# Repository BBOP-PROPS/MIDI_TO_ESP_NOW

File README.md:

# MIDI_TO_ESP_NOW
Intercept MIDI Keyboard Key Press and cause an action on a remote ESP Device.  

[ESP-NOW](https://www.espressif.com/en/products/software/esp-now/overview)

[ESP-NOW Example](https://randomnerdtutorials.com/esp-now-esp32-arduino-ide/)

[MIDI with Arduino](https://www.instructables.com/Send-and-Receive-MIDI-with-Arduino/)

When a student plays a key on the MIDI Keyboard, it should send a remote action throuh the ESP-NOW protocol.  Pressing the keyboard "C" key might turn on a light momentarily on a remote prop.  "D" might turn on a stepper motor on a different prop.

The "Master" will interface with the MIDI keyboard, and the majority of the programming will be on the Slaves.

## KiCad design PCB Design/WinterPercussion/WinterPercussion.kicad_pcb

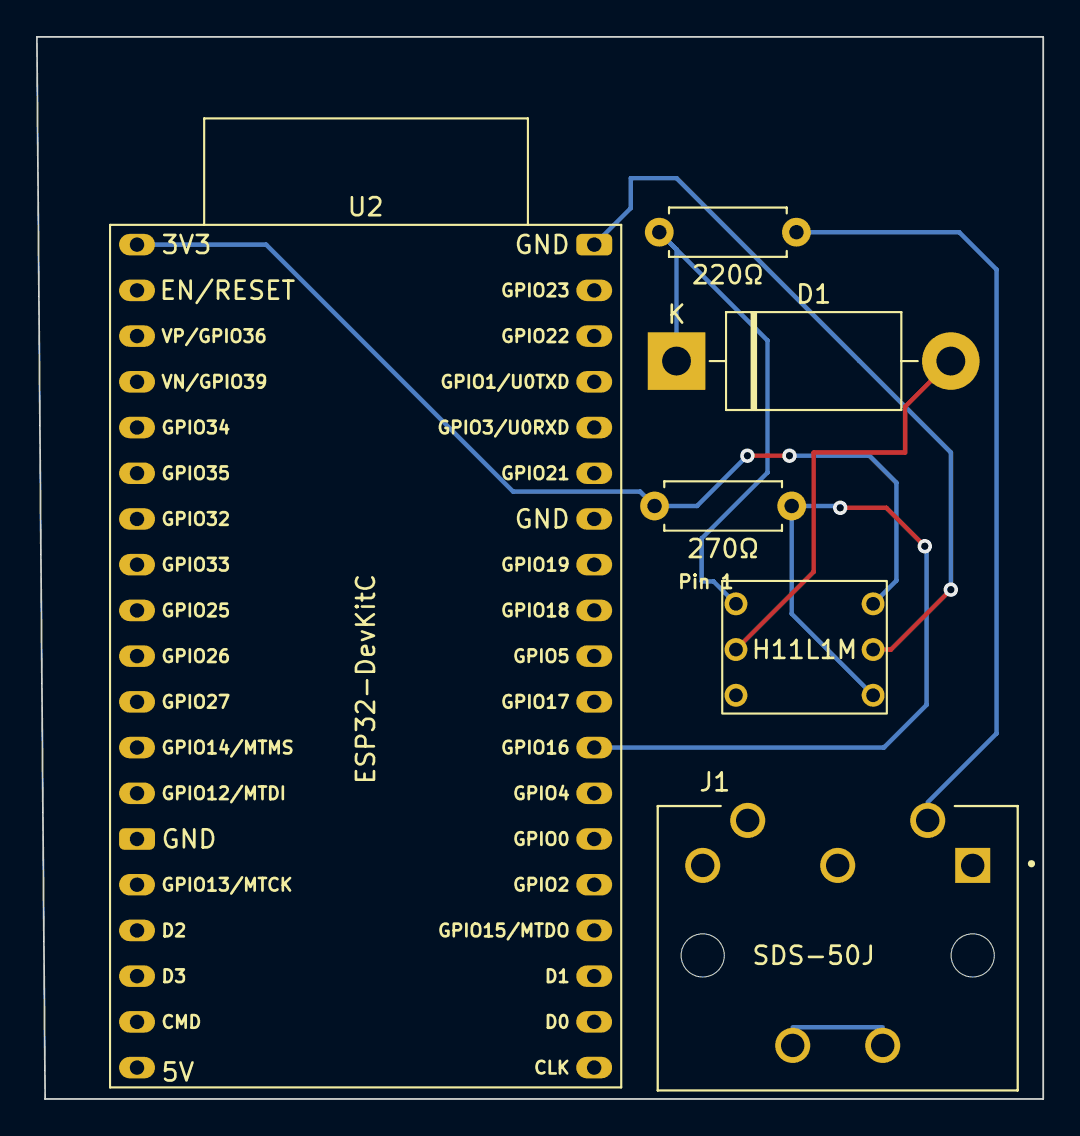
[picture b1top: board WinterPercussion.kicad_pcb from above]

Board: 2 copper layers, 55.9 x 59.0 mm, 6 parts (0 on the bottom side), 6 nets.

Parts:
D1: DIODE; D_DO-201AD_P15.24mm_Horizontal
J1: SDS-50J; CUI_SDS-50J
R1: 220Ω; R_Axial_DIN0207_L6.3mm_D2.5mm_P7.62mm_Horizontal
R2: 270Ω; R_Axial_DIN0207_L6.3mm_D2.5mm_P7.62mm_Horizontal
U1: H11L1M
U2: ESP32-DevKitC

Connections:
+3V3: R2.1, U1.6 (VCC), U2.1 (3V3)
ESP_PIN: R2.2, U1.4 (VO), U2.27 (GPIO16)
GND: U1.5 (GND), U2.38 (GND)
unnamed: J1.4, R1.2
unnamed: D1.2 (A), U1.2 (CATHODE)
unnamed: D1.1 (K), R1.1, U1.1 (ANODE)

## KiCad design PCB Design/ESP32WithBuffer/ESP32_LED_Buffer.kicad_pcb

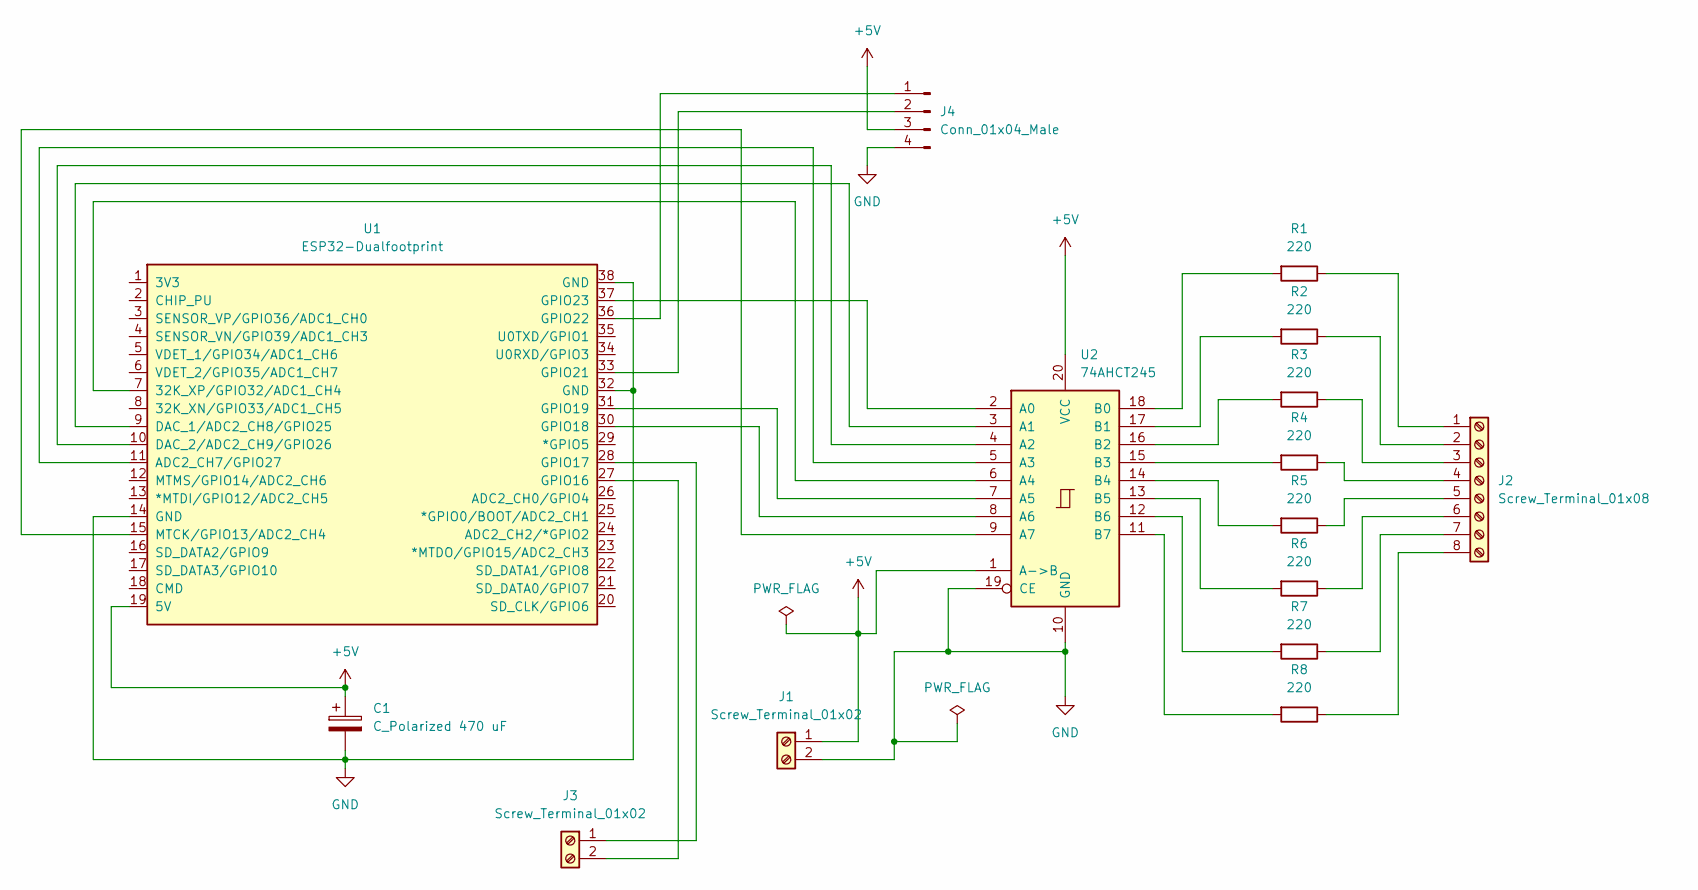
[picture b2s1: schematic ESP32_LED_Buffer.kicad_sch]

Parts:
C1: C_Polarized 470 uF; CP_Radial_D13.0mm_P7.50mm
J1, J3: Screw_Terminal_01x02; TerminalBlock_RND_205-00287_1x02_P5.08mm_Horizontal
J2: Screw_Terminal_01x08; TerminalBlock_RND_205-00293_1x08_P5.08mm_Horizontal
J4: Conn_01x04_Male; PinHeader_1x04_P2.54mm_Vertical
R1, R2, R3, R4, R5, R6, R7, R8: 220; R_Axial_DIN0207_L6.3mm_D2.5mm_P10.16mm_Horizontal
U1: ESP32-Dualfootprint; ESP32-DualFootprint
U2: 74AHCT245; DIP-20_W7.62mm

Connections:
+5V: C1.1, J1.1, J4.3, U1.19 (5V), U2.1 (A->B), U2.20 (VCC)
GND: C1.2, J1.2, J4.4, U1.14 (GND), U1.32 (GND), U1.38 (GND), U2.10 (GND), U2.19 (CE)
unnamed: J2.1, R1.1
unnamed: J2.2, R2.1
unnamed: J2.3, R3.1
unnamed: J2.4, R4.1
unnamed: J2.5, R5.1
unnamed: J2.6, R6.1
unnamed: J2.7, R7.1
unnamed: J2.8, R8.1
unnamed: R1.2, U2.18 (B0)
unnamed: R2.2, U2.17 (B1)
unnamed: R3.2, U2.16 (B2)
unnamed: R4.2, U2.15 (B3)
unnamed: R5.2, U2.14 (B4)
unnamed: R6.2, U2.13 (B5)
unnamed: R7.2, U2.12 (B6)
unnamed: R8.2, U2.11 (B7)
unnamed: J3.2, U1.27 (GPIO16)
unnamed: J3.1, U1.28 (GPIO17)
unnamed: J4.2, U1.33 (GPIO21)
unnamed: J4.1, U1.36 (GPIO22)
unnamed: U1.37 (GPIO23), U2.2 (A0)
unnamed: U1.9 (DAC_1/ADC2_CH8/GPIO25), U2.3 (A1)
unnamed: U1.10 (DAC_2/ADC2_CH9/GPIO26), U2.4 (A2)
unnamed: U1.11 (ADC2_CH7/GPIO27), U2.5 (A3)
unnamed: U1.7 (32K_XP/GPIO32/ADC1_CH4), U2.6 (A4)
unnamed: U1.31 (GPIO19), U2.7 (A5)
unnamed: U1.30 (GPIO18), U2.8 (A6)
unnamed: U1.15 (MTCK/GPIO13/ADC2_CH4), U2.9 (A7)

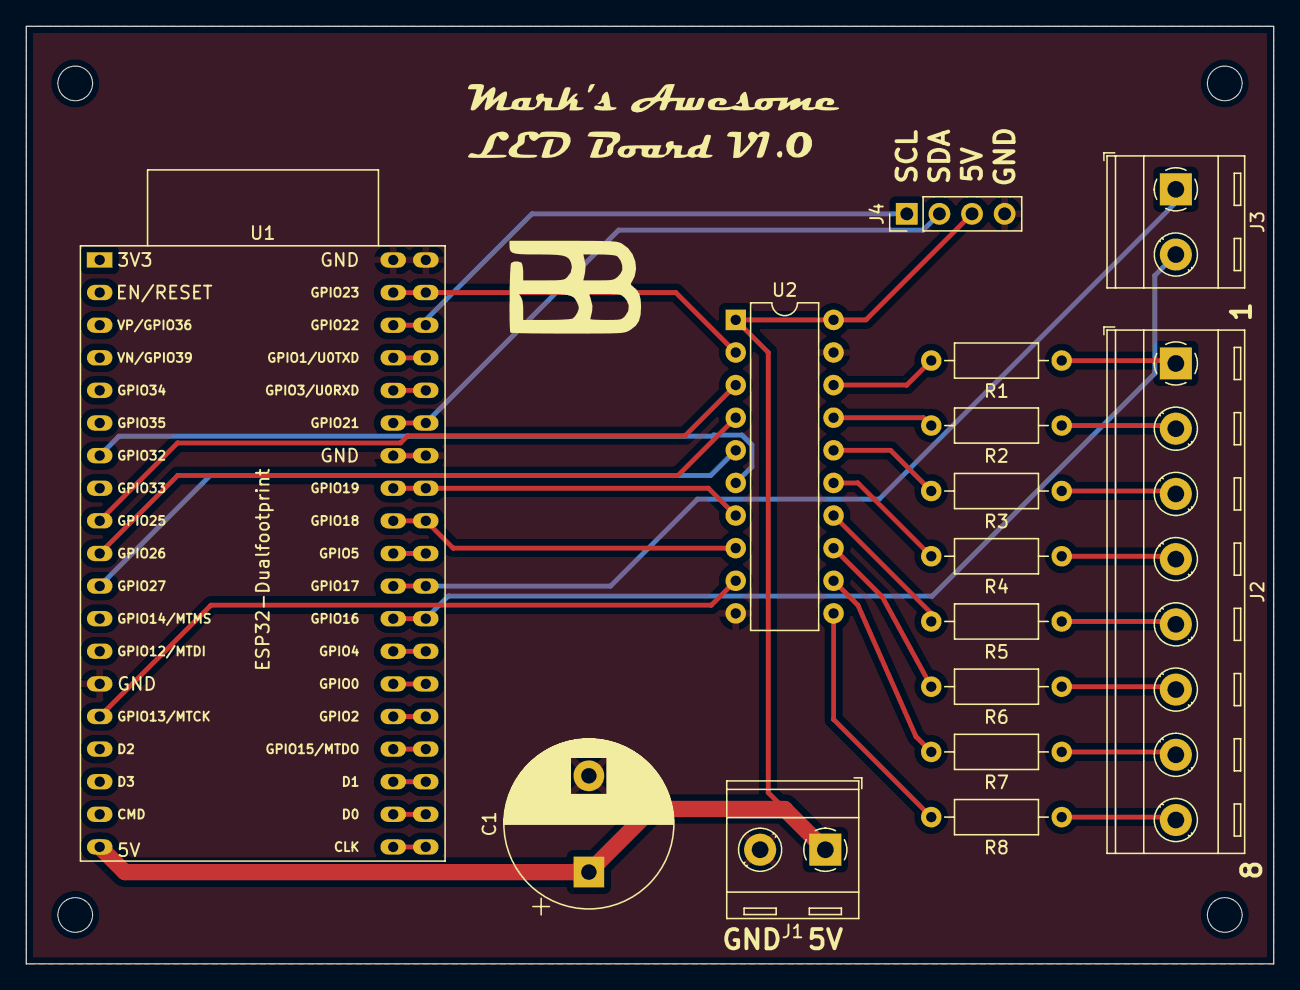
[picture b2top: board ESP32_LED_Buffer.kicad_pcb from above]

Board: 2 copper layers, 97.2 x 73.0 mm, 15 parts (0 on the bottom side), 30 nets.

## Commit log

2022-11-19 Send/Receive now working
2022-11-29 Demo of keyboard sending MIDI information and lighting an LED strip.
2022-11-29 PCB changes
2022-11-30 Board Design
2022-11-30 PDF's for design
2022-11-30 Updated with Pin16 from Mark
2022-12-02 Updated KiCad Docs
2022-12-02 Changed to 3.3v
2023-01-09 PCB Design Changes
2023-01-22 Send and receive code used during prop construction
2023-01-22 Cleaned up a little and make sure LEDs are off before starting the radio
2023-01-23 PCB Design Updates
2023-01-23 Our LEDs are RGB not GRB
2023-01-23 Diode UPdate
2023-01-24 Support toggle switch
2023-01-26 Bug, what bug?
2023-02-05 PCB for ESP32 board with buffer for LEDs
2023-02-05 State of code when MIDI equipment was delivered on 2/4/2023
2023-02-06 Code cleanup and add OFF command and timeout
2023-02-08 Added flash feature
2023-02-28 Updated effects based on John Marque input.
2023-03-02 Updates based on Zach's score
2023-03-08 A little documentation
2023-03-09 latest PCB changes.
2023-03-09 fixed number of led's for main branch.
2023-03-15 warm white color changes
2023-03-16 volume control for brightness
2023-03-16 added break; changed # of leds
2023-03-18 peer changes and knob working
2023-03-19 send 2x commands to ensure delivery.
2023-03-22 DEBUG and isolated Serial Prints
2023-03-24 Use macros for debug printing so they can easily be disabled for shows.
2023-03-26 Update transition time to part 3 per Zach's request.
2023-03-26 Fixed bug when using really long blend times
2023-03-27 Implemented retry mechanism
2023-03-28 Implement LED monitor for transmitter
2023-04-01 Increase retries
2023-04-02 Change WiFi channel to 6.
2023-04-07 Let's go with lucky 13 to avoid standard WiFi channels.
2023-04-08 Updates for Outro colors
2023-04-13 Remove monitor from transmitter
2023-04-15 First attempt at re-broadcasting messages between rings.
2023-04-19 Restart the ESP32 if there is a problem during initialization.
2023-04-19 Throttle the brightness setting
2023-04-21 Implement kill switch by using brightness
2023-04-21 Key # changes for kill switch

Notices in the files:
parts and their libraries:
Copyright 2021 Accelerated Designs. All rights reserved.
